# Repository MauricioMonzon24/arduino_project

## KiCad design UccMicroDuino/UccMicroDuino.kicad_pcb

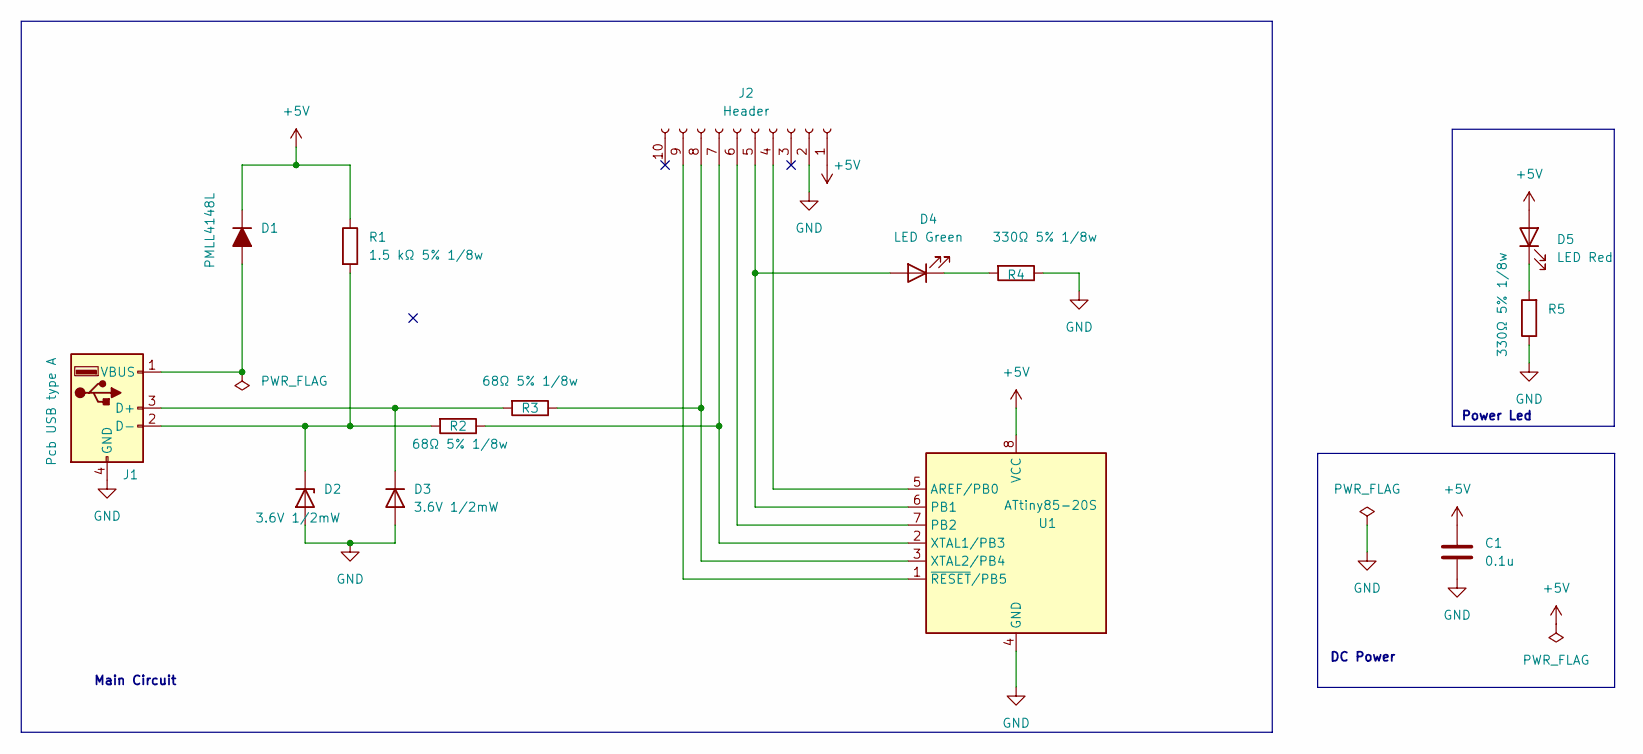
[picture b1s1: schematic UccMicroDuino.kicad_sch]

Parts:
C1: 0.1u; C_0805_2012Metric_Pad1.18x1.45mm_HandSolder
D1: PMLL4148L; D_MiniMELF
D2, D3: 3.6V 1/2mW; D_SOD-123
D4: LED Green; ledSMD
D5: LED Red; ledSMD
J1: Pcb USB type A; USB_A_UCC
J2: Header; PinHeader_1x10_P2.54mm_Vertical
R1: 1.5 kΩ 5% 1/8w; R_0805_2012Metric_Pad1.20x1.40mm_HandSolder
R2, R3: 68Ω 5% 1/8w; R_0805_2012Metric_Pad1.20x1.40mm_HandSolder
R4, R5: 330Ω 5% 1/8w; R_0805_2012Metric_Pad1.20x1.40mm_HandSolder
U1: ATtiny85-20S; SOIC-8_5.3x5.3mm_P1.27mm

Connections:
+5V: C1.1, D1.1 (K), D5.2 (A), J2.1, R1.1, U1.8 (VCC)
GND: C1.2, D2.2 (A), D3.2 (A), J1.4 (GND), J2.2, R4.1, R5.1, U1.4 (GND)
unnamed: D1.2 (A), J1.1 (VBUS)
unnamed: D2.1 (K), J1.2 (D-), R1.2, R2.2
unnamed: D3.1 (K), J1.3 (D+), R3.2
unnamed: D4.2 (A), J2.5, U1.6 (PB1)
unnamed: D4.1 (K), R4.2
unnamed: D5.1 (K), R5.2
unnamed: J2.4, U1.5 (AREF/PB0)
unnamed: J2.6, U1.7 (PB2)
unnamed: J2.7, R2.1, U1.2 (XTAL1/PB3)
unnamed: J2.8, R3.1, U1.3 (XTAL2/PB4)
unnamed: J2.9, U1.1 (~RESET/PB5)

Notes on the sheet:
DC Power
Power Led
Main Circuit

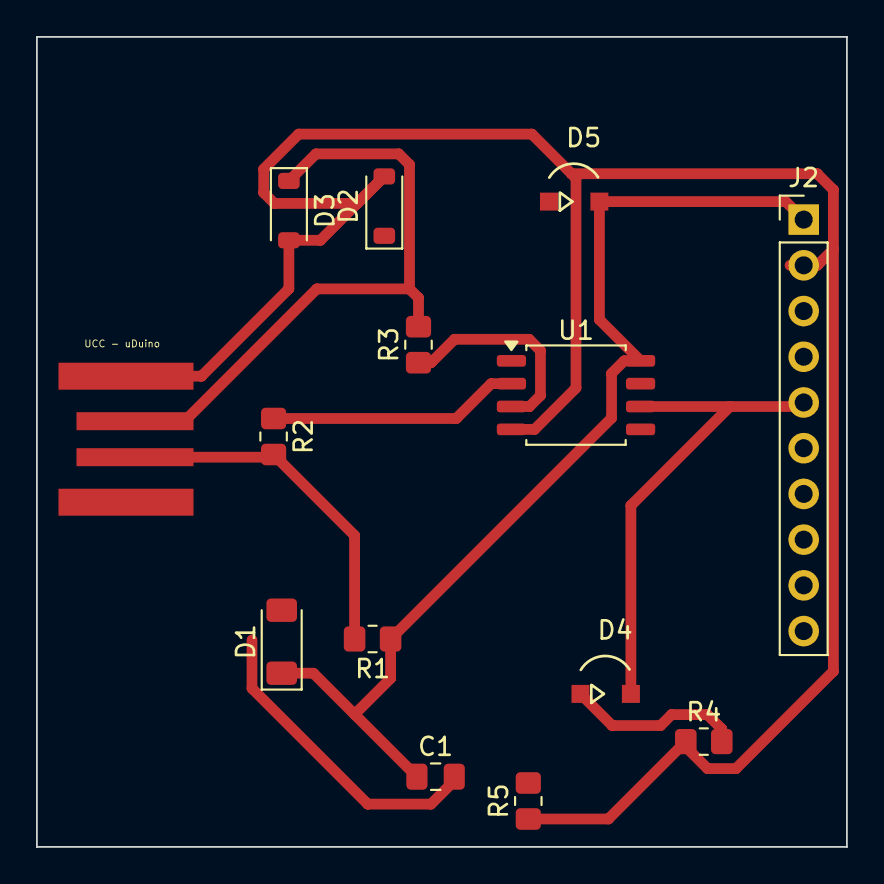
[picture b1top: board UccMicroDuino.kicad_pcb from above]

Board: 2 copper layers, 45.0 x 45.0 mm, 14 parts (0 on the bottom side), 13 nets.

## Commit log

2026-03-30 Agrego .gitignore para KiCad
2026-04-06 Esquematico principal completo con Power Led y DC Power
2026-04-06 Limpieza: excluir .DS_Store y .history del repositorio
2026-04-13 Esquematico principal terminado
2026-04-13 Comienzo de cableado
2026-04-15 avance ruteo
2026-04-25 PCB: Ruteo Completo, 0 errores
